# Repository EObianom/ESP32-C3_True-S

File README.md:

# ESP32-C3_True-S
This is an ESP32-C3 Development Board is based on the MINI-1

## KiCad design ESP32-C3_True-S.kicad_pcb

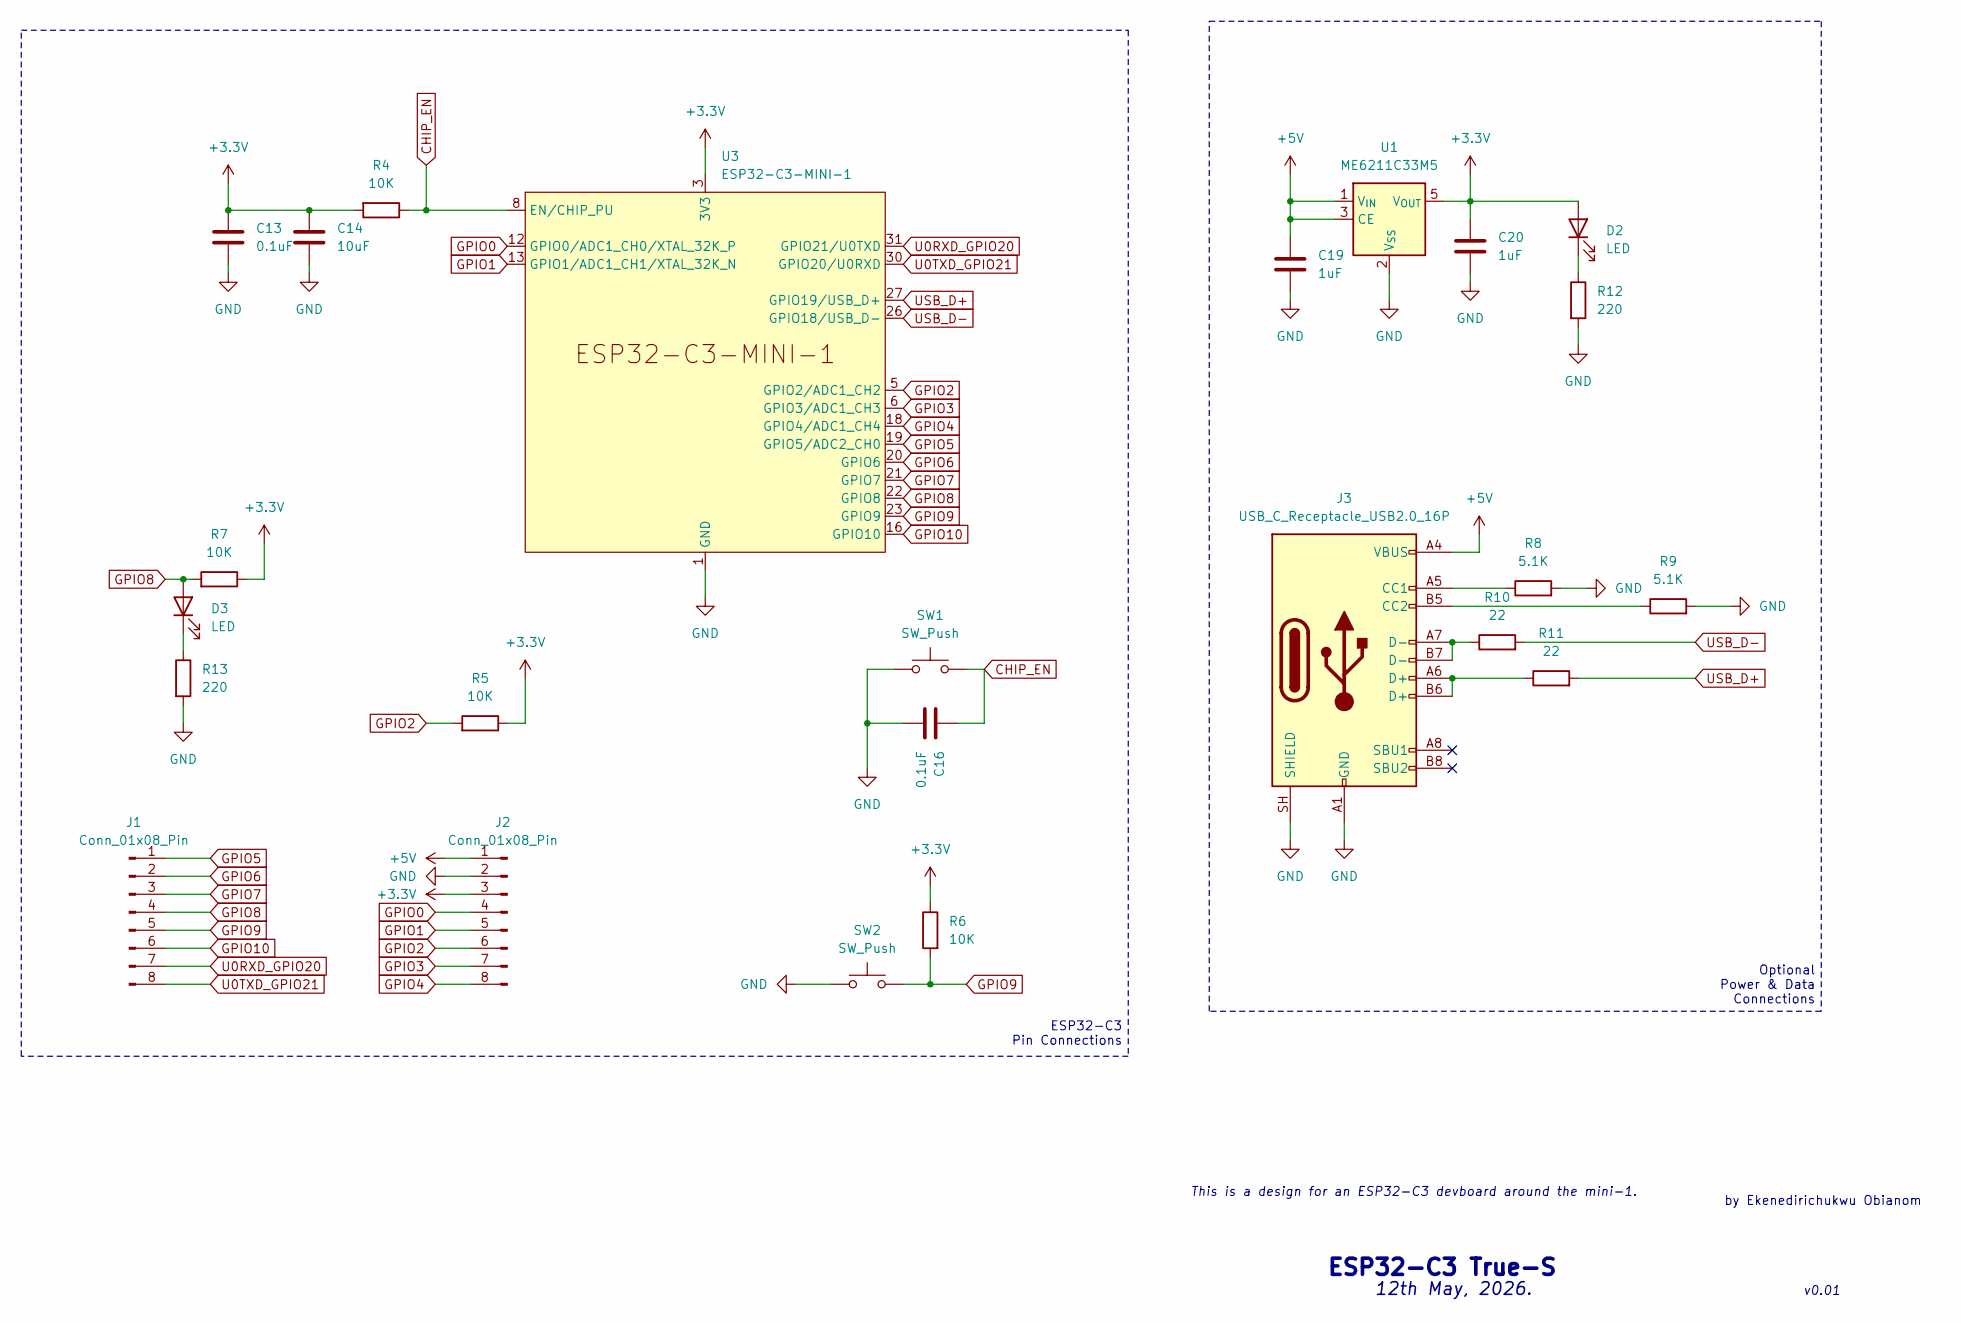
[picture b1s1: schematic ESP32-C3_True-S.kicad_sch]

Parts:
C13, C16: 0.1uF; C_0402_1005Metric
C14: 10uF; C_0402_1005Metric
C19, C20: 1uF; C_0402_1005Metric
D2, D3: LED; LED_0603_1608Metric
J1, J2: Conn_01x08_Pin; PinHeader_1x08_P2.54mm_Vertical
J3: USB_C_Receptacle_USB2.0_16P; USB_C_Receptacle_HRO_TYPE-C-31-M-12
R4, R5, R6, R7: 10K; R_0402_1005Metric
R8, R9: 5.1K; R_0402_1005Metric
R10, R11: 22; R_0402_1005Metric
R12, R13: 220; R_0402_1005Metric
SW1, SW2: SW_Push; SW_Push_SPST_NO_Alps_SKRK
U1: ME6211C33M5; SOT-23-5
U3: ESP32-C3-MINI-1

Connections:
+3.3V: C13.1, C14.1, C20.1, D2.2 (A), J2.3, R4.2, R5.1, R6.1, R7.1, U1.5 (V_{OUT}), U3.3 (3V3)
+5V: C19.1, J2.1, J3.A4 (VBUS), J3.A9 (VBUS), J3.B4 (VBUS), J3.B9 (VBUS), U1.1 (V_{IN}), U1.3 (CE)
CHIP_EN: C16.1, R4.1, SW1.2, U3.8 (EN/CHIP_PU)
GND: C13.2, C14.2, C16.2, C19.2, C20.2, J2.2, J3.A1 (GND), J3.A12 (GND), J3.B1 (GND), J3.B12 (GND), J3.SH (SHIELD), R8.2, R9.2, R12.2, R13.2, SW1.1, SW2.1, U1.2 (V_{SS}), U3.1 (GND), U3.2 (GND), U3.11 (GND), U3.14 (GND), U3.36 (GND), U3.37 (GND), U3.38 (GND), U3.39 (GND), U3.40 (GND), U3.41 (GND), U3.42 (GND), U3.43 (GND), U3.44 (GND), U3.45 (GND), U3.46 (GND), U3.47 (GND), U3.48 (GND), U3.49 (GND), U3.50 (GND), U3.51 (GND), U3.52 (GND), U3.53 (GND)
GPIO0: J2.4, U3.12 (GPIO0/ADC1_CH0/XTAL_32K_P)
GPIO1: J2.5, U3.13 (GPIO1/ADC1_CH1/XTAL_32K_N)
GPIO2: J2.6, R5.2, U3.5 (GPIO2/ADC1_CH2)
GPIO3: J2.7, U3.6 (GPIO3/ADC1_CH3)
GPIO4: J2.8, U3.18 (GPIO4/ADC1_CH4)
GPIO5: J1.1, U3.19 (GPIO5/ADC2_CH0)
GPIO6: J1.2, U3.20 (GPIO6)
GPIO7: J1.3, U3.21 (GPIO7)
GPIO8: D3.2 (A), J1.4, R7.2, U3.22 (GPIO8)
GPIO9: J1.5, R6.2, SW2.2, U3.23 (GPIO9)
GPIO10: J1.6, U3.16 (GPIO10)
unnamed: D2.1 (K), R12.1
unnamed: D3.1 (K), R13.1
unnamed: J3.A5 (CC1), R8.1
unnamed: J3.B5 (CC2), R9.1
unnamed: J3.A6 (D+), J3.B6 (D+), R11.1
unnamed: J3.A7 (D-), J3.B7 (D-), R10.1
U0RXD_GPIO20: J1.7, U3.31 (GPIO21/U0TXD)
U0TXD_GPIO21: J1.8, U3.30 (GPIO20/U0RXD)
USB_D+: R11.2, U3.27 (GPIO19/USB_D+)
USB_D-: R10.2, U3.26 (GPIO18/USB_D-)

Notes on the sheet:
v0.01
ESP32-C3 Pin Connections
12th May, 2026.
This is a design for an ESP32-C3 devboard around the mini-1.
Optional Power & Data Connections
by Ekenedirichukwu Obianom
ESP32-C3 True-S

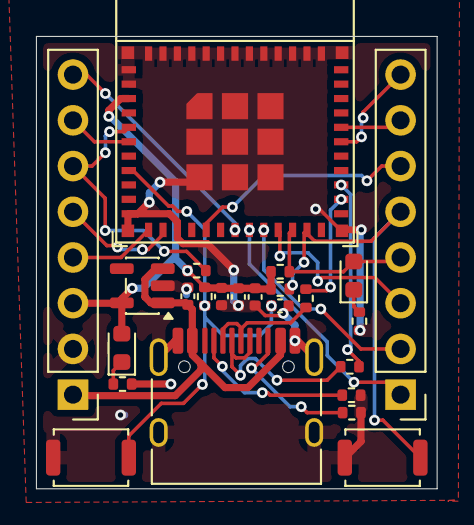
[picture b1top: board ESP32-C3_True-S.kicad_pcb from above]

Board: 2 copper layers, 22.3 x 25.1 mm, 24 parts (0 on the bottom side), 25 nets.

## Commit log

2026-05-13 Version 1
    This is the first update.
2026-05-13 Add image to README.md
    Added an image to the README file.
